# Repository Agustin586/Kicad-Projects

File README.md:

# Kicad-Projects
Aca se encuentran los diseños de pcb de kicad

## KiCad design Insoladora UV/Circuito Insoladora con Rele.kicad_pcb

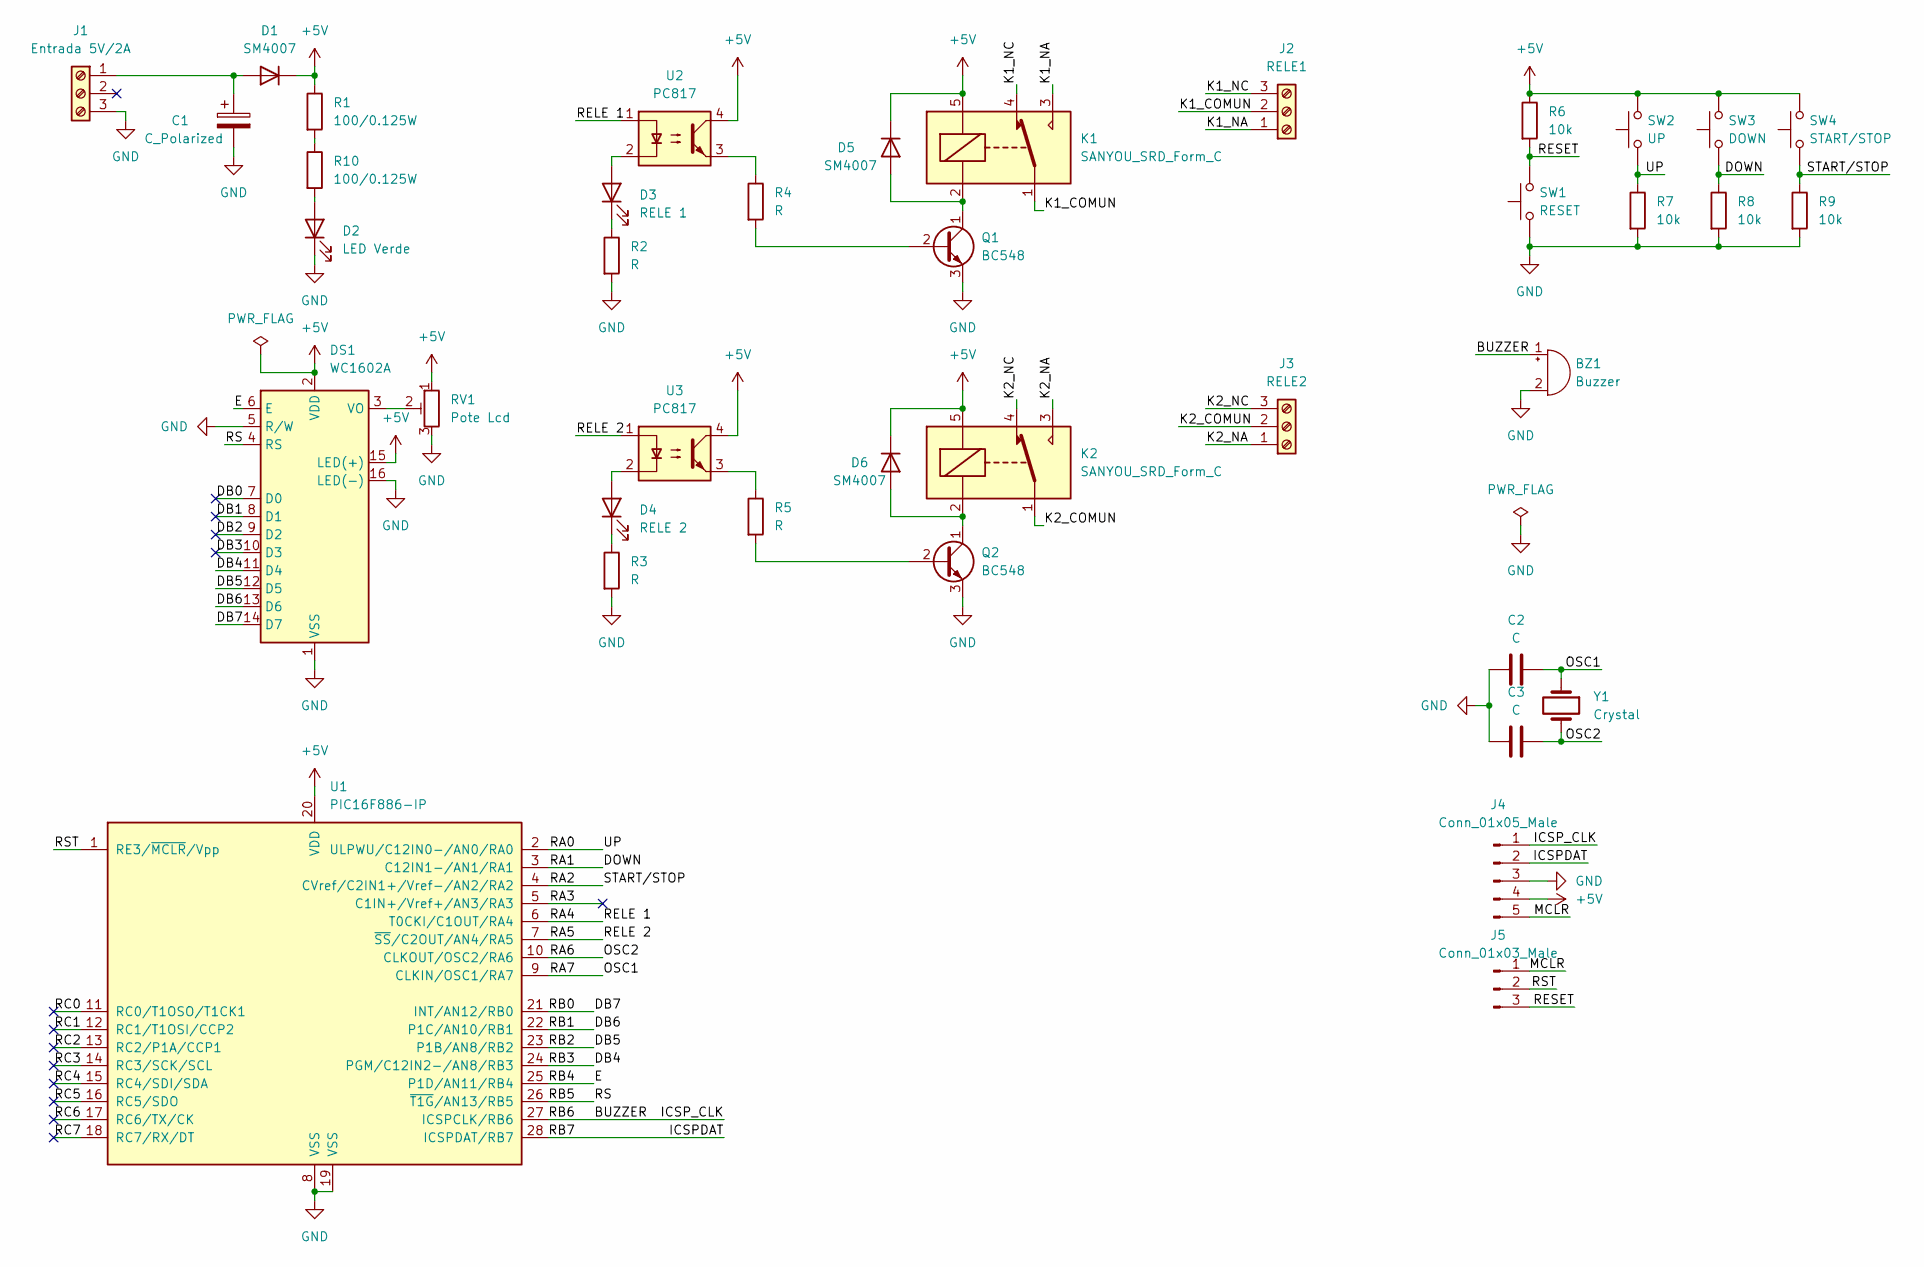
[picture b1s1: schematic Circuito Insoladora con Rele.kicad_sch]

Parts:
BZ1: Buzzer; Buzzer_12x9.5RM7.6
C1: C_Polarized; CP_Radial_D8.0mm_P2.50mm
C2, C3: C; C_Disc_D4.7mm_W2.5mm_P5.00mm
D1, D5, D6: SM4007; D_MELF
D2: LED Verde; LED_0805_2012Metric
D3: RELE 1; LED_D5.0mm
D4: RELE 2; LED_D5.0mm
DS1: WC1602A
J1: Entrada 5V/2A; TerminalBlock_Phoenix_PT-1,5-3-5.0-H_1x03_P5.00mm_Horizontal
J2: RELE1; TerminalBlock_Phoenix_PT-1,5-3-5.0-H_1x03_P5.00mm_Horizontal
J3: RELE2; TerminalBlock_Phoenix_PT-1,5-3-5.0-H_1x03_P5.00mm_Horizontal
J4: Conn_01x05_Male; PinHeader_1x05_P2.54mm_Vertical
J5: Conn_01x03_Male; PinHeader_1x03_P2.54mm_Vertical
K1, K2: SANYOU_SRD_Form_C; Relay_SPDT_SANYOU_SRD_Series_Form_C
Q1, Q2: BC548; TO-92_Inline_Wide
R1, R10: 100/0.125W; R_0805_2012Metric
R2, R3, R4, R5: R; R_Axial_DIN0207_L6.3mm_D2.5mm_P10.16mm_Horizontal
R6, R7, R8, R9: 10k; R_0805_2012Metric
RV1: Pote Lcd; Potentiometer_Piher_PT-10-H05_Horizontal
SW1: RESET; SW_PUSH_6mm
SW2: UP; SW_PUSH_6mm
SW3: DOWN; SW_PUSH_6mm
SW4: START/STOP; SW_PUSH_6mm
U1: PIC16F886-IP; DIP-28_W7.62mm_LongPads
U2, U3: PC817; DIP-4_W7.62mm_LongPads
Y1: Crystal; Crystal_HC52-8mm_Vertical

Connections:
+5V: D1.1 (K), D5.1 (K), D6.1 (K), DS1.2 (VDD), DS1.15 (LED(+)), J4.4, K1.5, K2.5, R1.1, R6.1, RV1.1, SW2.2, SW3.2, SW4.2, U1.20 (VDD), U2.4, U3.4
/DB0: DS1.7 (D0)
/DB1: DS1.8 (D1)
/DB2: DS1.9 (D2)
/DB3: DS1.10 (D3)
/DB4: DS1.11 (D4), U1.24 (PGM/C12IN2-/AN8/RB3)
/DB5: DS1.12 (D5), U1.23 (P1B/AN8/RB2)
/DB6: DS1.13 (D6), U1.22 (P1C/AN10/RB1)
/DB7: DS1.14 (D7), U1.21 (INT/AN12/RB0)
/DOWN: R8.1, SW3.1, U1.3 (C12IN1-/AN1/RA1)
/E: DS1.6 (E), U1.25 (P1D/AN11/RB4)
/ICSP_CLK: BZ1.1 (-), J4.1, U1.27 (ICSPCLK/RB6)
/K1_COMUN: J2.2, K1.1
/K1_NA: J2.1, K1.3
/K1_NC: J2.3, K1.4
/K2_COMUN: J3.2, K2.1
/K2_NA: J3.1, K2.3
/K2_NC: J3.3, K2.4
/MCLR: J4.5, J5.1
/OSC1: C2.2, U1.9 (CLKIN/OSC1/RA7), Y1.1
/OSC2: C3.2, U1.10 (CLKOUT/OSC2/RA6), Y1.2
/RA0: R7.1, SW2.1, U1.2 (ULPWU/C12IN0-/AN0/RA0)
/RA2: R9.1, SW4.1, U1.4 (CVref/C2IN1+/Vref-/AN2/RA2)
/RA3: U1.5 (C1IN+/Vref+/AN3/RA3)
/RA4: U1.6 (T0CKI/C1OUT/RA4), U2.1
/RA5: U1.7 (~SS/C2OUT/AN4/RA5), U3.1
/RB5: DS1.4 (RS), U1.26 (~T1G/AN13/RB5)
/RB7: J4.2, U1.28 (ICSPDAT/RB7)
/RC0: U1.11 (RC0/T1OSO/T1CK1)
/RC1: U1.12 (RC1/T1OSI/CCP2)
/RC2: U1.13 (RC2/P1A/CCP1)
/RC3: U1.14 (RC3/SCK/SCL)
/RC4: U1.15 (RC4/SDI/SDA)
/RC5: U1.16 (RC5/SDO)
/RC6: U1.17 (RC6/TX/CK)
/RC7: U1.18 (RC7/RX/DT)
/RESET: J5.3, R6.2, SW1.2
/RST: J5.2, U1.1 (RE3/~MCLR/Vpp)
GND: BZ1.2 (+), C1.2, C2.1, C3.1, D2.1 (K), DS1.1 (VSS), DS1.5 (R/W), DS1.16 (LED(-)), J1.3, J4.3, Q1.3 (E), Q2.3 (E), R2.2, R3.2, R7.2, R8.2, R9.2, RV1.3, SW1.1, U1.8 (VSS), U1.19 (VSS)
unnamed: C1.1, D1.2 (A), J1.1
unnamed: D2.2 (A), R10.2
unnamed: D3.1 (K), R2.1
unnamed: D3.2 (A), U2.2
unnamed: D4.1 (K), R3.1
unnamed: D4.2 (A), U3.2
unnamed: D5.2 (A), K1.2, Q1.1 (C)
unnamed: D6.2 (A), K2.2, Q2.1 (C)
unnamed: DS1.3 (VO), RV1.2
unnamed: Q1.2 (B), R4.2
unnamed: Q2.2 (B), R5.2
unnamed: R1.2, R10.1
unnamed: R4.1, U2.3
unnamed: R5.1, U3.3

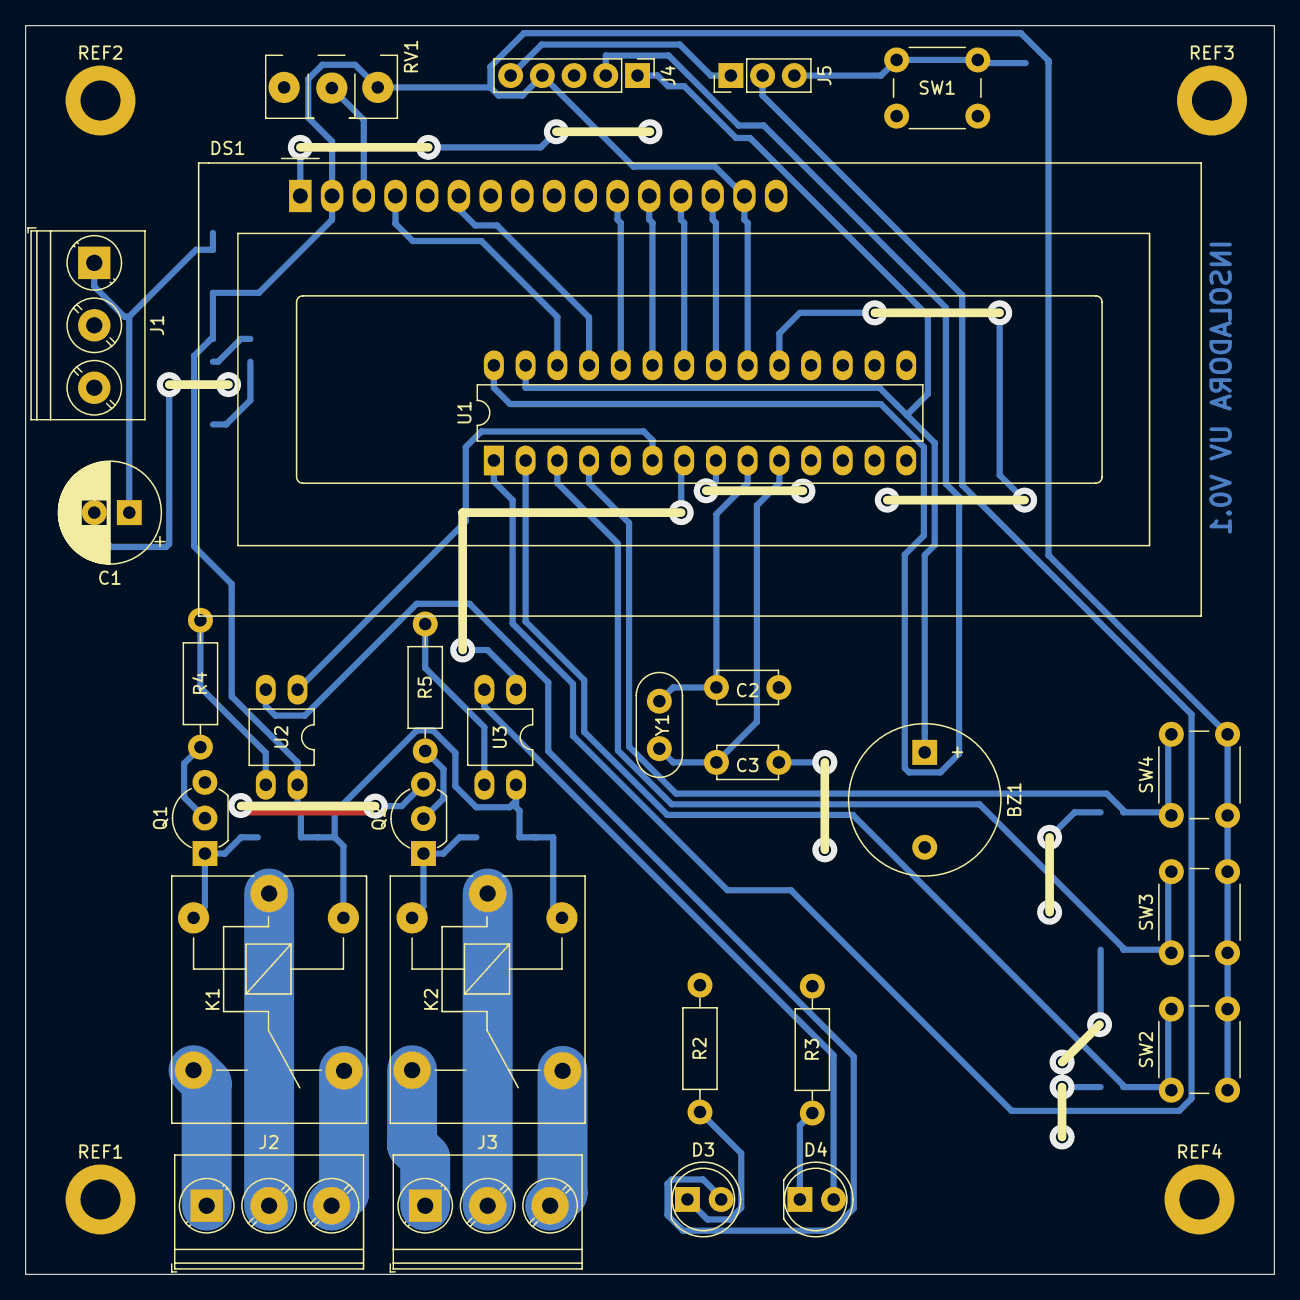
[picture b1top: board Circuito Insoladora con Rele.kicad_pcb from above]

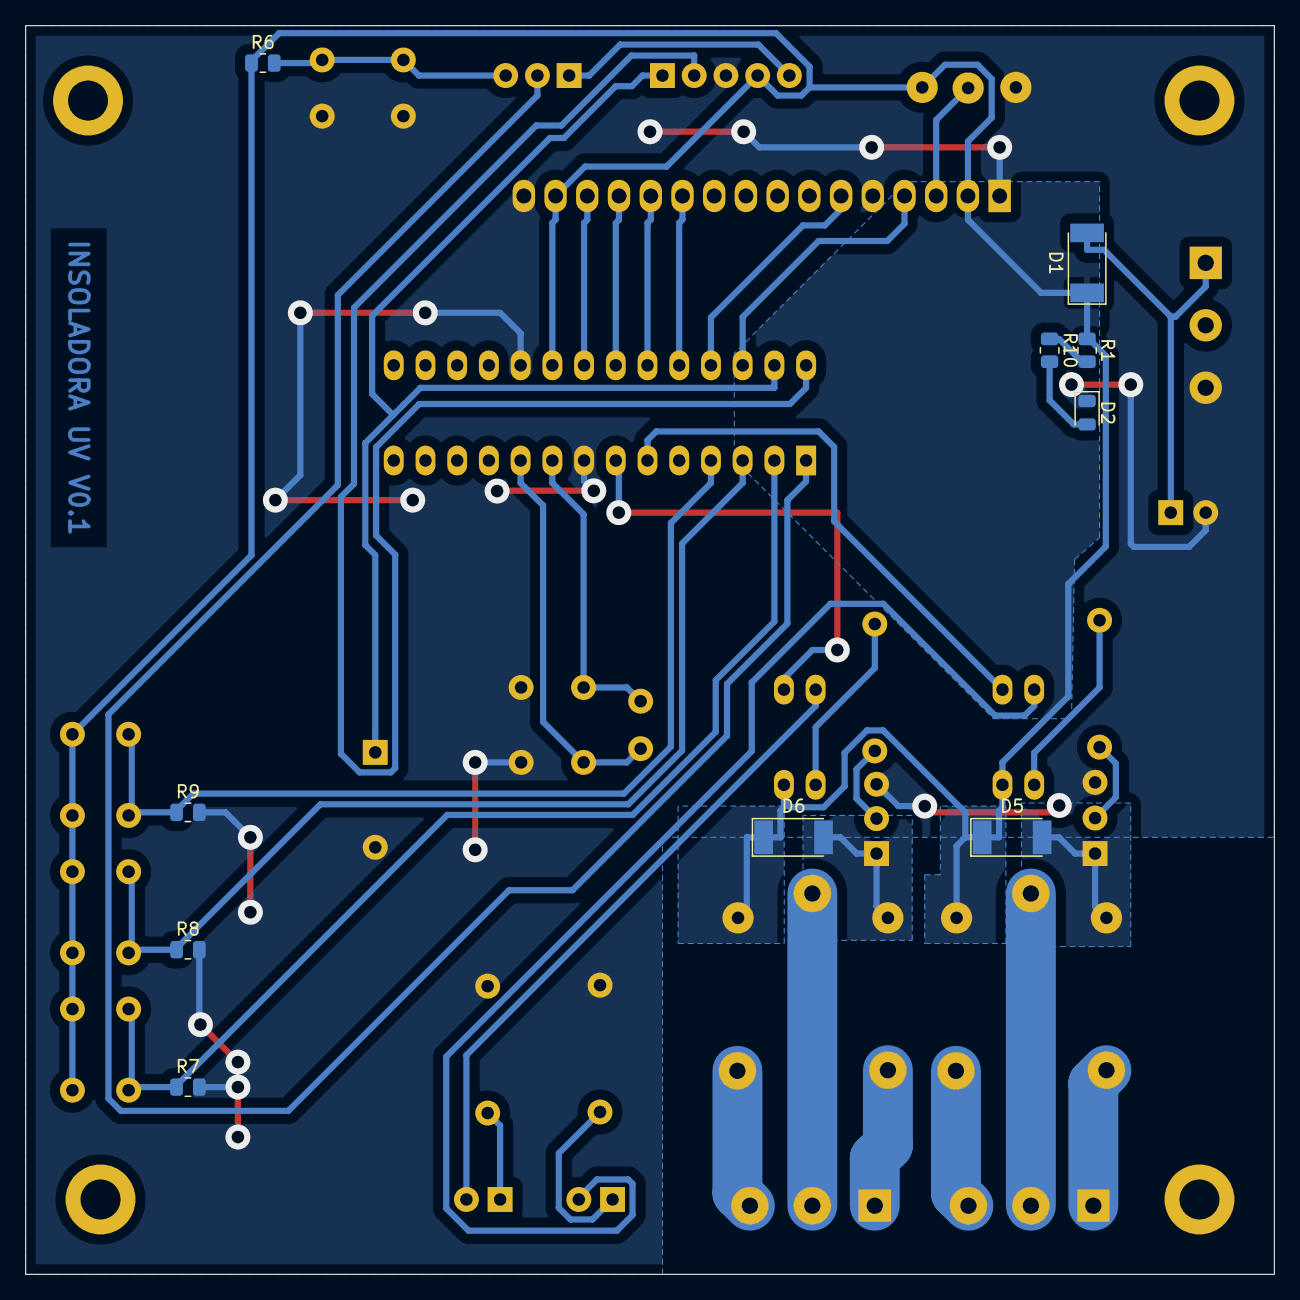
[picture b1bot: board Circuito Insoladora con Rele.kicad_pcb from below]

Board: 2 copper layers, 100.0 x 100.0 mm, 43 parts (10 on the bottom side), 40 nets.

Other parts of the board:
REF1, REF2, REF3, REF4: MountingHole_3.2mm_M3_DIN965_Pad

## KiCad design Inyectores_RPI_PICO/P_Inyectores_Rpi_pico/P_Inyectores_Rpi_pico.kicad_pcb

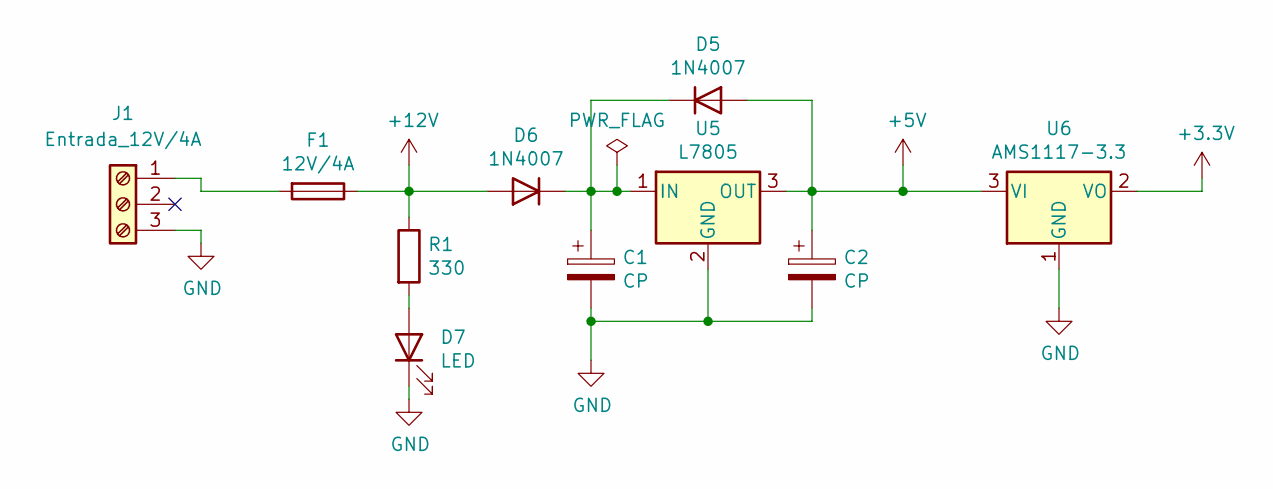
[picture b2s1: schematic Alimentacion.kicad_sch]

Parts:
C1, C2: CP; CP_Radial_D5.0mm_P2.00mm
D5, D6: 1N4007; D_DO-41_SOD81_P10.16mm_Horizontal
D7: LED; LED_D5.0mm
F1: 12V/4A; Fuse_SunFuse-6HP
J1: Entrada_12V/4A; TerminalBlock_Phoenix_PT-1,5-3-5.0-H_1x03_P5.00mm_Horizontal
R1: 330; R_Axial_DIN0207_L6.3mm_D2.5mm_P10.16mm_Horizontal
U5: L7805; TO-220-3_Vertical
U6: AMS1117-3.3; SOT-223-3_TabPin2

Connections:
+3V3: U6.2 (VO); also elsewhere on the board
+5V: C2.1, D5.2 (A), U5.3 (OUT), U6.3 (VI); also elsewhere on the board
+12V: D6.2 (A), F1.1, R1.1; also elsewhere on the board
GND: C1.2, C2.2, D7.1 (K), J1.3, U5.2 (GND), U6.1 (GND); also elsewhere on the board
unnamed: C1.1, D5.1 (K), D6.1 (K), U5.1 (IN)
unnamed: D7.2 (A), R1.2
unnamed: F1.2, J1.1

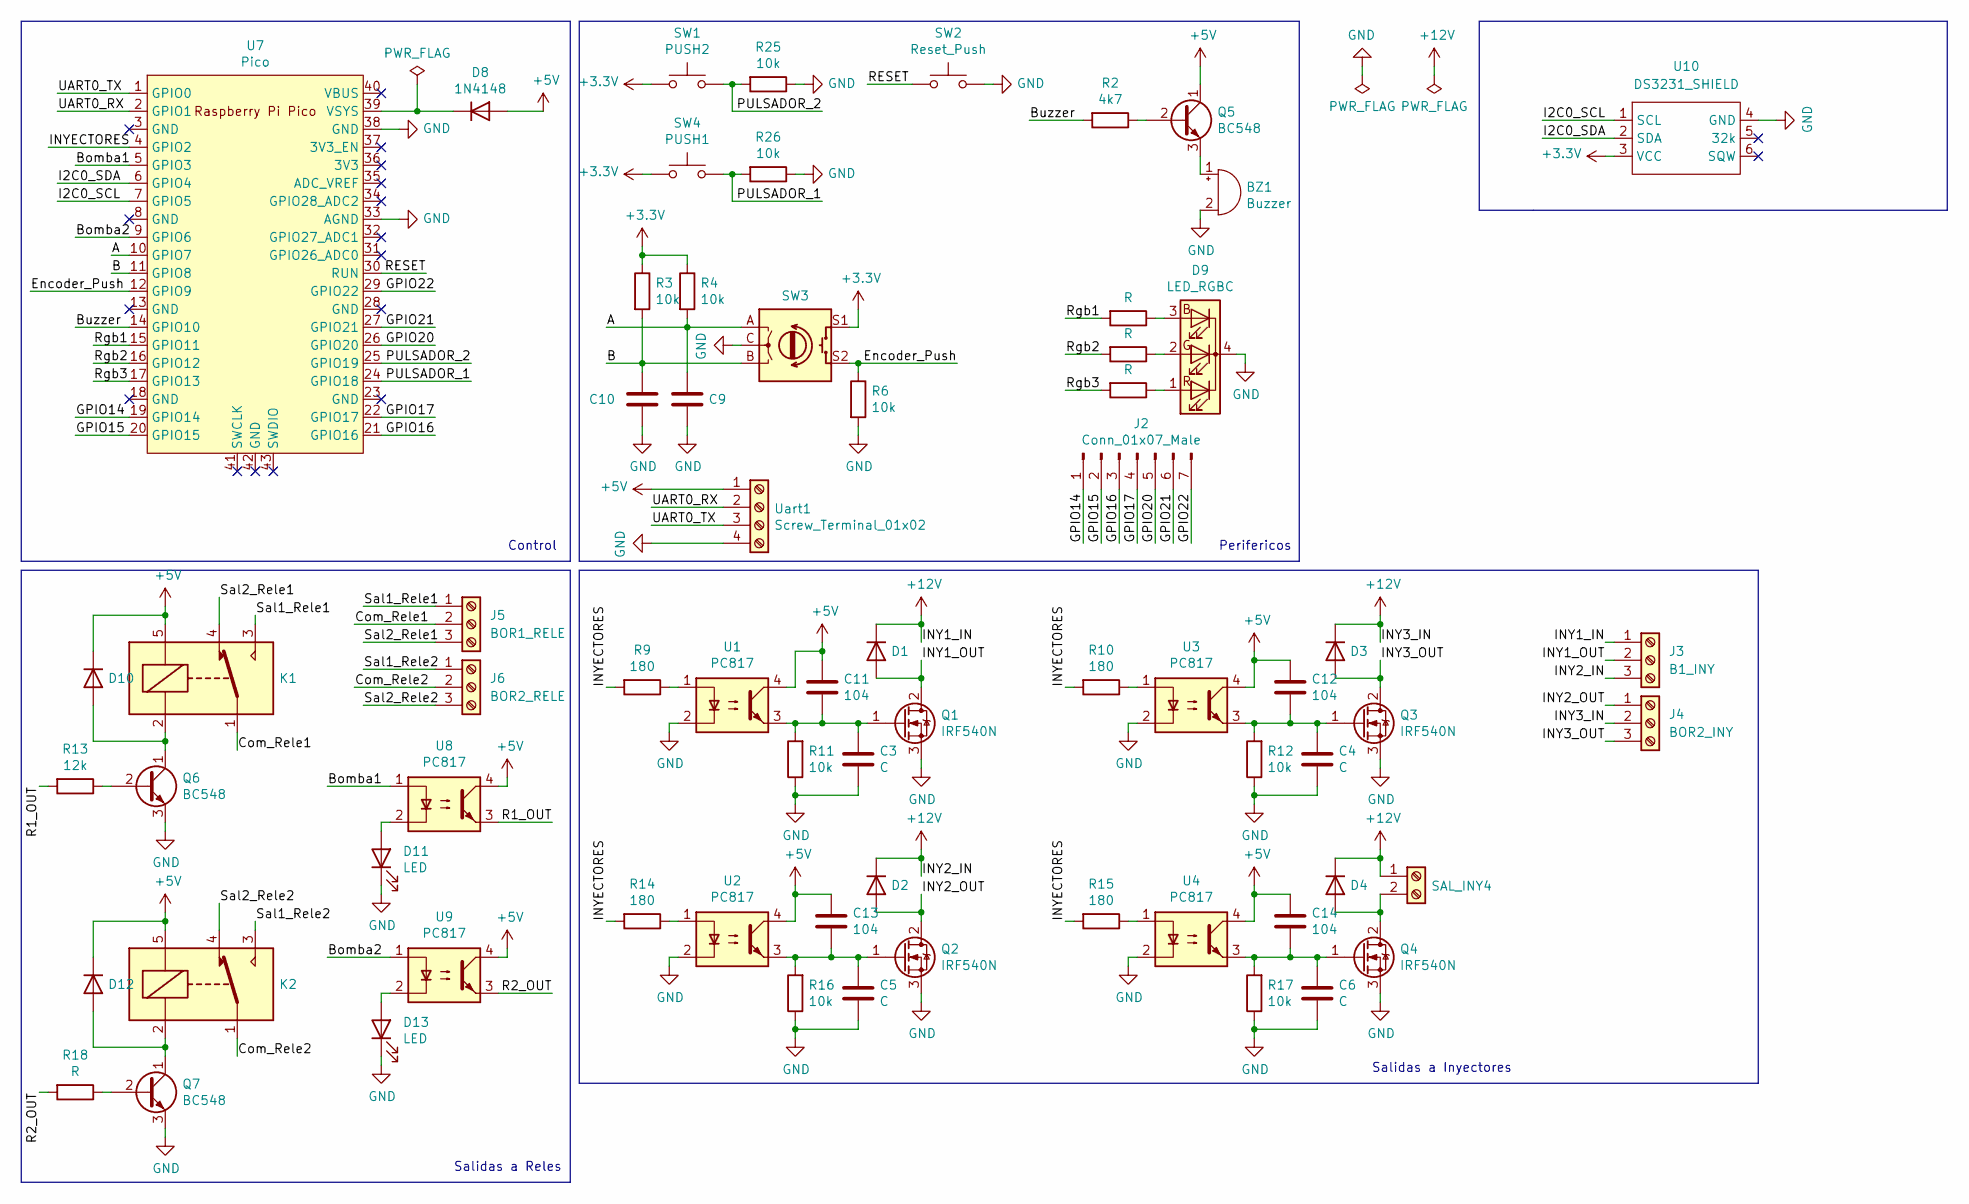
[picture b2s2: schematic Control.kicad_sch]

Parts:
BZ1: Buzzer; Buzzer_12x9.5RM7.6
C3, C4, C5, C6: C; C_Disc_D5.0mm_W2.5mm_P2.50mm
C9, C10, C11, C12, C13, C14: 104; C_Disc_D5.0mm_W2.5mm_P2.50mm
D1, D2, D3, D4, D10, D12: 1N4007; D_DO-41_SOD81_P10.16mm_Horizontal
D8: 1N4148; D_DO-35_SOD27_P7.62mm_Horizontal
D9: LED_RGBC; LED_D5.0mm-4_RGB_Wide_Pins
D11, D13: LED; LED_D5.0mm
J2: Conn_01x07_Male; PinSocket_1x07_P2.54mm_Vertical
J3: B1_INY; TerminalBlock_Phoenix_PT-1,5-3-5.0-H_1x03_P5.00mm_Horizontal
J4: BOR2_INY; TerminalBlock_Phoenix_PT-1,5-3-5.0-H_1x03_P5.00mm_Horizontal
J5: BOR1_RELE; TerminalBlock_Phoenix_PT-1,5-3-5.0-H_1x03_P5.00mm_Horizontal
J6: BOR2_RELE; TerminalBlock_Phoenix_PT-1,5-3-5.0-H_1x03_P5.00mm_Horizontal
K1, K2: SANYOU_SRD_Form_C; Relay_SPDT_SANYOU_SRD_Series_Form_C
Q1, Q2, Q3, Q4: IRF540N; TO-220-3_Vertical
Q5, Q6, Q7: BC548; TO-92_Inline_Wide
R2: 4k7; R_Axial_DIN0207_L6.3mm_D2.5mm_P10.16mm_Horizontal
R3, R4, R6, R11, R12, R16, R17, R25, R26: 10k; R_Axial_DIN0207_L6.3mm_D2.5mm_P10.16mm_Horizontal
R5, R7, R8, R18: R; R_Axial_DIN0207_L6.3mm_D2.5mm_P10.16mm_Horizontal
R9, R10, R14, R15: 180; R_Axial_DIN0207_L6.3mm_D2.5mm_P10.16mm_Horizontal
R13: 12k; R_Axial_DIN0207_L6.3mm_D2.5mm_P10.16mm_Horizontal
SAL_INY4: BOR3_INY; TerminalBlock_Phoenix_PT-1,5-2-5.0-H_1x02_P5.00mm_Horizontal
SW1: PUSH2; SW_PUSH_6mm
SW2: Reset_Push; SW_PUSH_6mm
SW3: Rotary_Encoder_Switch; RotaryEncoder_Alps_EC12E-Switch_Vertical_H20mm
SW4: PUSH1; SW_PUSH_6mm
U1, U2, U3, U4, U8, U9: PC817; DIP-4_W7.62mm_LongPads
U7: Pico; RPi_Pico_SMD_TH
U10: DS3231_SHIELD; DS3231_Shield
Uart1: Screw_Terminal_01x02; Molex_KK-254_AE-6410-04A_1x04_P2.54mm_Vertical

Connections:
+3V3: R3.1, R4.1, SW1.1, SW3.S1, SW4.1, U10.3 (VCC); also elsewhere on the board
+5V: C11.1, C12.1, C13.1, C14.1, D8.2 (A), D10.1 (K), D12.1 (K), K1.5, K2.5, Q5.1 (C), U1.4, U2.4, U3.4, U4.4, U8.4, U9.4, Uart1.1; also elsewhere on the board
+12V: D1.1 (K), D2.1 (K), D3.1 (K), D4.1 (K), J3.1, J3.3, J4.2, SAL_INY4.1; also elsewhere on the board
/Control/A: C9.1, R4.2, SW3.A, U7.10 (GPIO7)
/Control/B: C10.1, R3.2, SW3.B, U7.11 (GPIO8)
/Control/Bomba1: U7.5 (GPIO3), U8.1
/Control/Bomba2: U7.9 (GPIO6), U9.1
/Control/Buzzer: R2.2, U7.14 (GPIO10)
/Control/Com_Rele1: J5.2, K1.1
/Control/Com_Rele2: J6.2, K2.1
/Control/Encoder_Push: R6.1, SW3.S2, U7.12 (GPIO9)
/Control/GPIO14: J2.1, U7.19 (GPIO14)
/Control/GPIO15: J2.2, U7.20 (GPIO15)
/Control/GPIO16: J2.3, U7.21 (GPIO16)
/Control/GPIO17: J2.4, U7.22 (GPIO17)
/Control/GPIO20: J2.5, U7.26 (GPIO20)
/Control/GPIO21: J2.6, U7.27 (GPIO21)
/Control/GPIO22: J2.7, U7.29 (GPIO22)
/Control/I2C0_SCL: U7.7 (GPIO5), U10.1 (SCL)
/Control/I2C0_SDA: U7.6 (GPIO4), U10.2 (SDA)
/Control/INY1_OUT: D1.2 (A), J3.2, Q1.2 (D)
/Control/INY2_OUT: D2.2 (A), J4.1, Q2.2 (D)
/Control/INY3_OUT: D3.2 (A), J4.3, Q3.2 (D)
/Control/INYECTORES: R9.2, R10.2, R14.2, R15.2, U7.4 (GPIO2)
/Control/PULSADOR_1: R26.2, SW4.2, U7.24 (GPIO18)
/Control/PULSADOR_2: R25.2, SW1.2, U7.25 (GPIO19)
/Control/R1_OUT: R13.2, U8.3
/Control/R2_OUT: R18.2, U9.3
/Control/RESET: SW2.1, U7.30 (RUN)
/Control/Rgb1: R5.2, U7.15 (GPIO11)
/Control/Rgb2: R7.2, U7.16 (GPIO12)
/Control/Rgb3: R8.2, U7.17 (GPIO13)
/Control/Sal1_Rele1: J5.1, K1.3
/Control/Sal1_Rele2: J6.1, K2.3
/Control/Sal2_Rele1: J5.3, K1.4
/Control/Sal2_Rele2: J6.3, K2.4
/Control/UART0_RX: U7.2 (GPIO1), Uart1.2
/Control/UART0_TX: U7.1 (GPIO0), Uart1.3
GND: BZ1.2 (+), C3.2, C4.2, C5.2, C6.2, C9.2, C10.2, D9.4 (K), D11.1 (K), D13.1 (K), Q1.3 (S), Q2.3 (S), Q3.3 (S), Q4.3 (S), Q6.3 (E), Q7.3 (E), R6.2, R11.1, R12.1, R16.1, R17.1, R25.1, R26.1, SW2.2, SW3.C, U1.2, U2.2, U3.2, U4.2, U7.33 (AGND), U7.38 (GND), U10.4 (GND), Uart1.4; also elsewhere on the board
unnamed: BZ1.1 (-), Q5.3 (E)
unnamed: C3.1, C11.2, Q1.1 (G), R11.2, U1.3
unnamed: C4.1, C12.2, Q3.1 (G), R12.2, U3.3
unnamed: C5.1, C13.2, Q2.1 (G), R16.2, U2.3
unnamed: C6.1, C14.2, Q4.1 (G), R17.2, U4.3
unnamed: D4.2 (A), Q4.2 (D), SAL_INY4.2
unnamed: D8.1 (K), U7.39 (VSYS)
unnamed: D9.1 (RA), R8.1
unnamed: D9.2 (GA), R7.1
unnamed: D9.3 (BA), R5.1
unnamed: D10.2 (A), K1.2, Q6.1 (C)
unnamed: D11.2 (A), U8.2
unnamed: D12.2 (A), K2.2, Q7.1 (C)
unnamed: D13.2 (A), U9.2
unnamed: Q5.2 (B), R2.1
unnamed: Q6.2 (B), R13.1
unnamed: Q7.2 (B), R18.1
unnamed: R9.1, U1.1
unnamed: R10.1, U3.1
unnamed: R14.1, U2.1
unnamed: R15.1, U4.1

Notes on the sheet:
Salidas a Inyectores
Control
Salidas a Reles
Perifericos

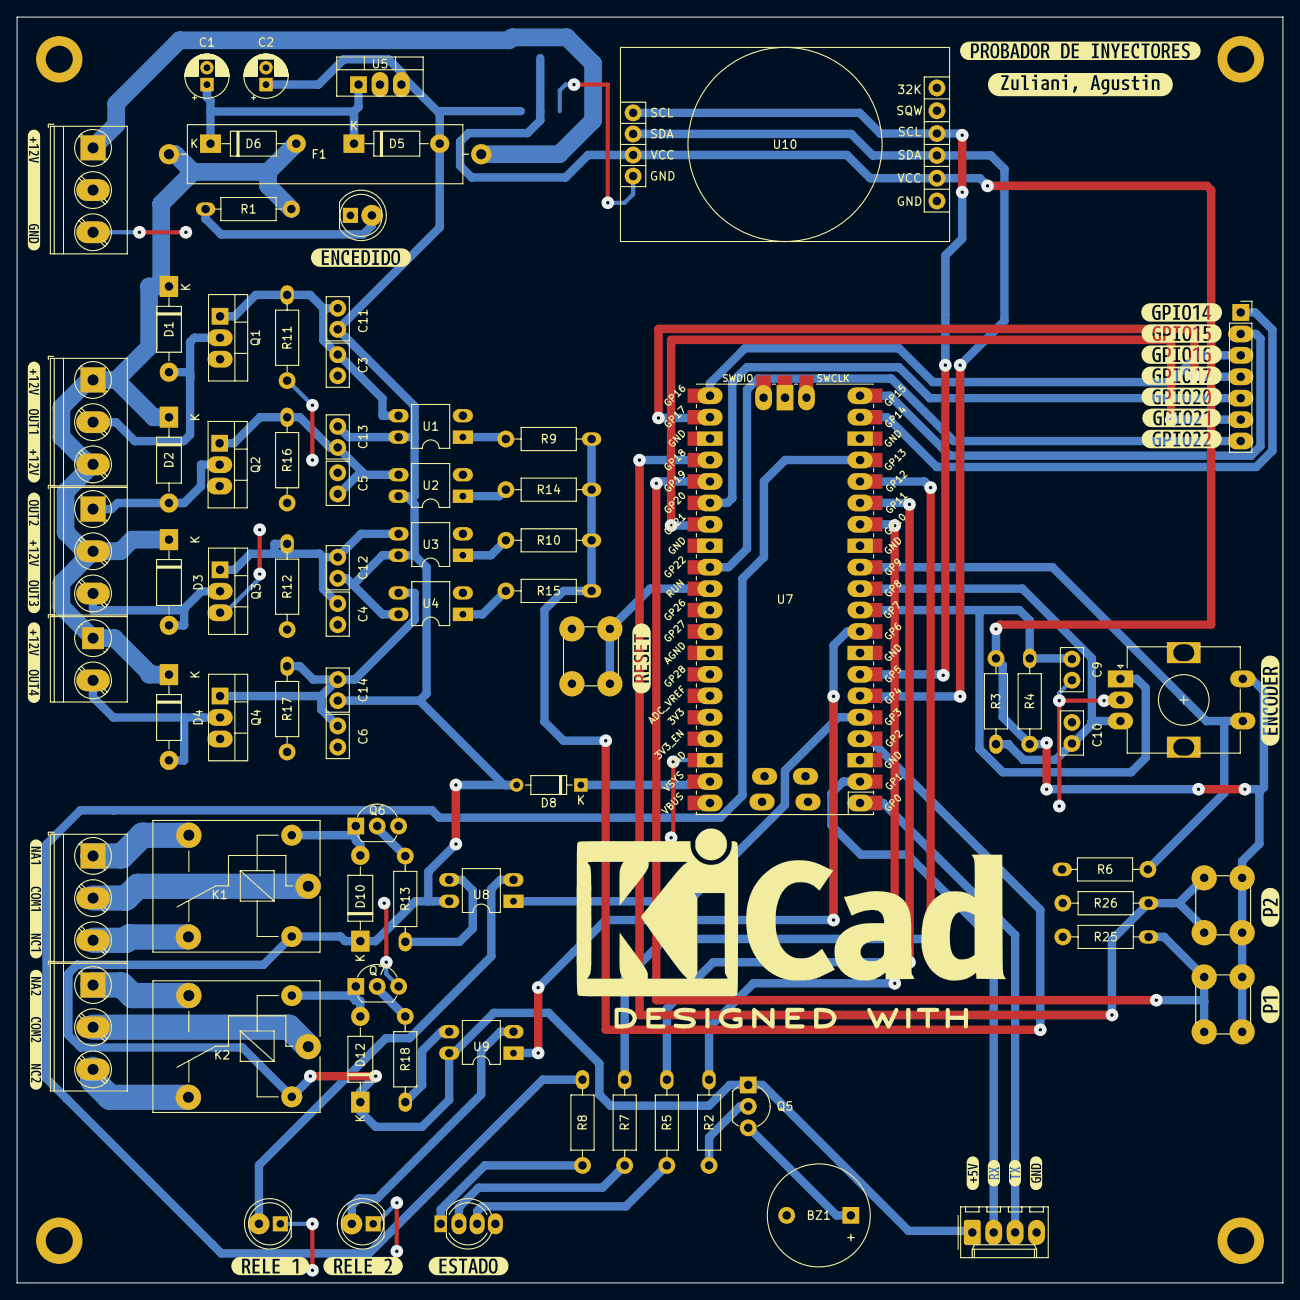
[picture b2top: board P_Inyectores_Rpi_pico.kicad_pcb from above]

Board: 2 copper layers, 150.0 x 150.0 mm, 109 parts (1 on the bottom side), 63 nets.

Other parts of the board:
REF1: KiCad-Logo2_20mm_SilkScree; KiCad-Logo2_20mm_SilkScreen
REF3, REF4, REF5: MountingHole_3.2mm_M3_ISO14580_Pad
kibuzzard-62C09A4A: G***; kibuzzard-62C09A4A
kibuzzard-62C09A65: G***; kibuzzard-62C09A65
kibuzzard-62C095A2: G***; kibuzzard-62C095A2
kibuzzard-62C095AC: G***; kibuzzard-62C095AC
kibuzzard-62C095B6: G***; kibuzzard-62C095B6
kibuzzard-62C095BF: G***; kibuzzard-62C095BF
kibuzzard-62C095C6: G***; kibuzzard-62C095C6
kibuzzard-62C095D0: G***; kibuzzard-62C095D0
kibuzzard-62C095D9: G***; kibuzzard-62C095D9
kibuzzard-62C096C0: G***; kibuzzard-62C096C0
kibuzzard-62C096D5: G***; kibuzzard-62C096D5
kibuzzard-62C096DE: G***; kibuzzard-62C096DE
kibuzzard-62C096F9: G***; kibuzzard-62C096F9
kibuzzard-62C098BB: G***; kibuzzard-62C098BB
kibuzzard-62C099B8: G***; kibuzzard-62C099B8
kibuzzard-62C099BF: G***; kibuzzard-62C099BF
kibuzzard-62C099C8: G***; kibuzzard-62C099C8
kibuzzard-62C099DD: G***; kibuzzard-62C099DD
kibuzzard-62C0966F: G***; kibuzzard-62C0966F
kibuzzard-62C09447: G***; kibuzzard-62C09447
kibuzzard-62C09473: G***; kibuzzard-62C09473
kibuzzard-62C09649: G***; kibuzzard-62C09649
kibuzzard-62C09656: G***; kibuzzard-62C09656
kibuzzard-62C09664: G***; kibuzzard-62C09664
kibuzzard-62C09818: G***; kibuzzard-62C09818
kibuzzard-62C09846: G***; kibuzzard-62C09846
kibuzzard-62C09983: G***; kibuzzard-62C09983

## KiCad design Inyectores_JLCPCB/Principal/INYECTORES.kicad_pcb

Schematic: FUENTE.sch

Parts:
D7, D9: 1N5408; D_DO-201AD_P15.24mm_Horizontal
D8: 1N4007; D_DO-41_SOD81_P10.16mm_Horizontal
ENTRADA_RELE1: Screw_Terminal_01x02; bornera_tornillos_1x02
J1: Screw_Terminal_01x03; bornera_tornillos_1x03
R1, R2: 440; R_Axial_DIN0207_L6.3mm_D2.5mm_P10.16mm_Horizontal
RL1: JW2; Relay_DPDT_Panasonic_JW2
ROJO1: LED; LED_D5.0mm
SALIDA_RELE1: Screw_Terminal_01x02; bornera_tornillos_1x02
SW1: SW_Push; SW_PUSH_6mm
VERDE1: LED; LED_D5.0mm

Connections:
unnamed 30: D7.2 (A), ENTRADA_RELE1.1; also elsewhere on the board
unnamed 46: R1.1; also elsewhere on the board
RELE1: R2.2, VERDE1.2 (A); also elsewhere on the board
RELE2: R1.2, ROJO1.2 (A); also elsewhere on the board

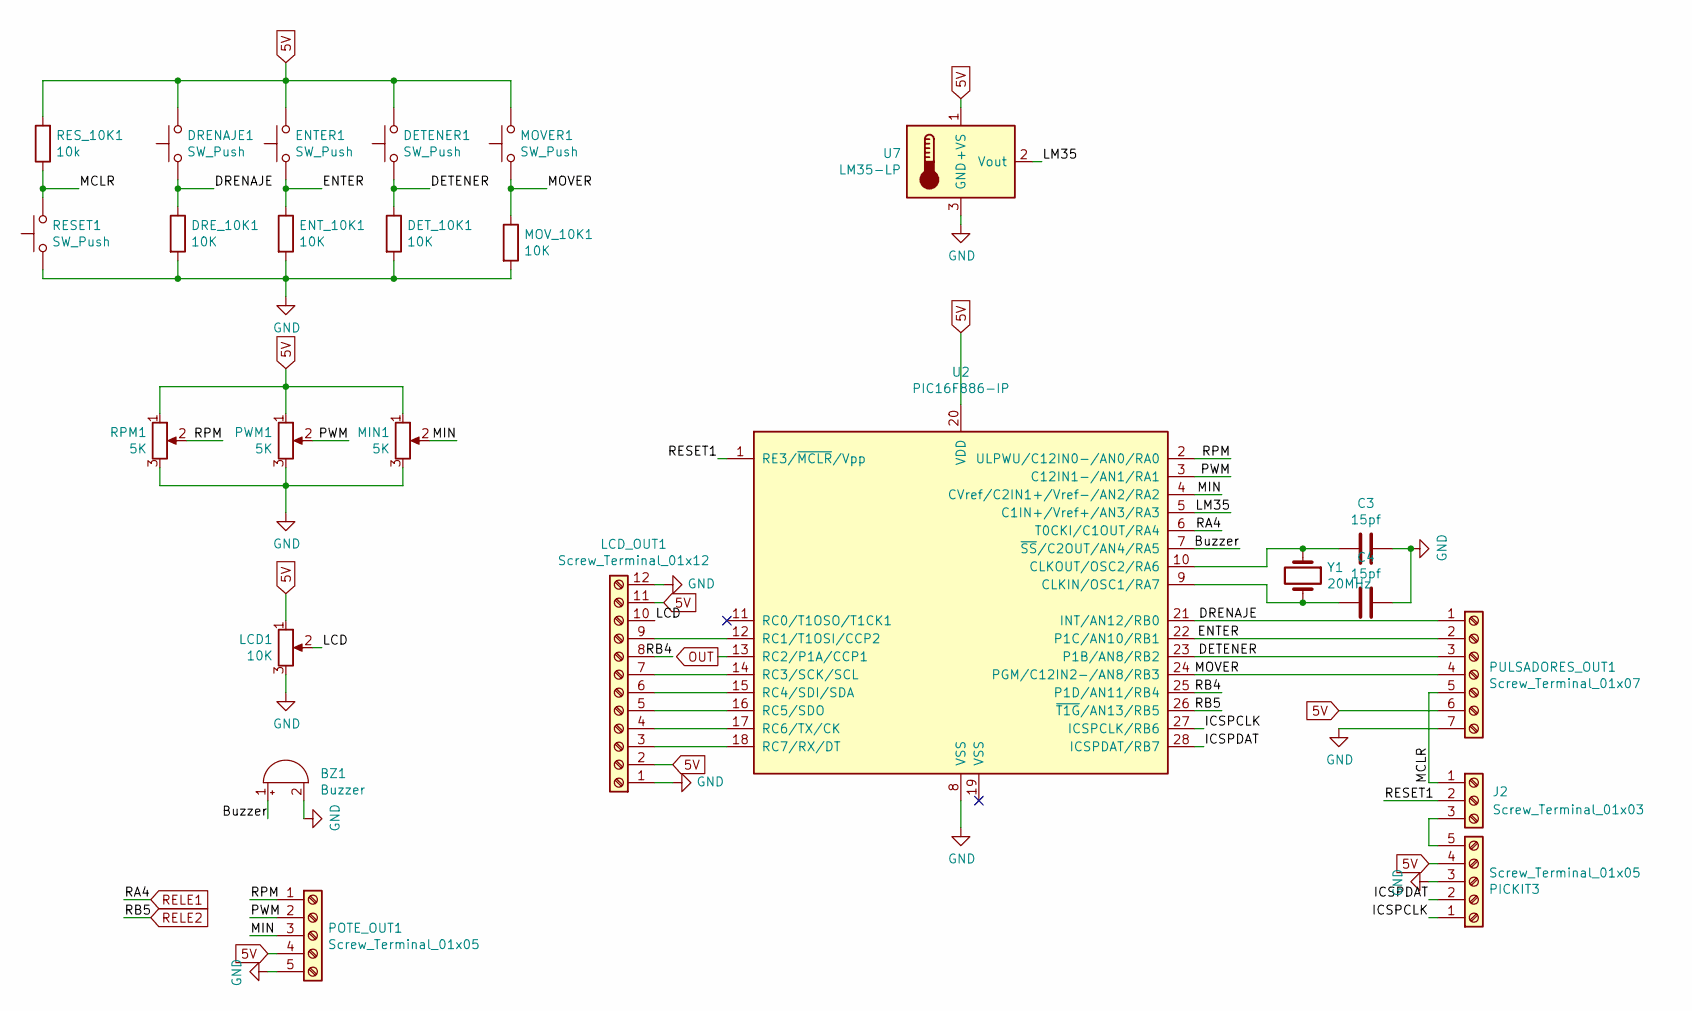
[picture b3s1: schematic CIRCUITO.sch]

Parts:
BZ1: Buzzer; Buzzer_12x9.5RM7.6
C3, C4: 15pf; C_Disc_D3.0mm_W2.0mm_P2.50mm
DETENER1: SW_Push; SW_PUSH_6mm
DET_10K1: 10K; R_Axial_DIN0207_L6.3mm_D2.5mm_P10.16mm_Horizontal
DRENAJE1: SW_Push; SW_PUSH_6mm
DRE_10K1: 10K; R_Axial_DIN0207_L6.3mm_D2.5mm_P10.16mm_Horizontal
ENTER1: SW_Push; SW_PUSH_6mm
ENT_10K1: 10K; R_Axial_DIN0207_L6.3mm_D2.5mm_P10.16mm_Horizontal
J2: Screw_Terminal_01x03; PinHeader_1x03_P2.54mm_Vertical
LCD1: 10K; Potentiometer_Bourns_3296W_Vertical
LCD_OUT1: Screw_Terminal_01x12; PinSocket_1x12_P2.54mm_Vertical
MIN1: 5K; Potentiometer_Alps_RK163_Single_Horizontal
MOVER1: SW_Push; SW_PUSH_6mm
MOV_10K1: 10K; R_Axial_DIN0207_L6.3mm_D2.5mm_P10.16mm_Horizontal
PICKIT3: Screw_Terminal_01x05; PinHeader_1x05_P2.54mm_Horizontal
POTE_OUT1: Screw_Terminal_01x05; PinSocket_1x05_P2.54mm_Vertical
PULSADORES_OUT1: Screw_Terminal_01x07; PinSocket_1x07_P2.54mm_Vertical
PWM1: 5K; Potentiometer_Alps_RK163_Single_Horizontal
RESET1: SW_Push; SW_PUSH_6mm
RES_10K1: 10k; R_Axial_DIN0207_L6.3mm_D2.5mm_P10.16mm_Horizontal
RPM1: 5K; Potentiometer_Alps_RK163_Single_Horizontal
U2: PIC16F886-IP; DIP-28_W7.62mm_LongPads
U7: LM35-LP; TO-92L_Inline_Wide
Y1: 20MHz; Crystal_HC18-U_Vertical

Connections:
5V: DETENER1.2, DRENAJE1.2, ENTER1.2, LCD1.1, LCD_OUT1.2, LCD_OUT1.11, MIN1.1, MOVER1.2, PICKIT3.4, POTE_OUT1.4, PULSADORES_OUT1.6, PWM1.1, RES_10K1.2, RPM1.1, U2.20 (VDD), U7.1 (+VS); also elsewhere on the board
/CIRCUITO/Buzzer: BZ1.1 (-), U2.7 (~SS~/C2OUT/AN4/RA5)
/CIRCUITO/DETENER: DETENER1.1, DET_10K1.1, PULSADORES_OUT1.3, U2.23 (P1B/AN8/RB2)
/CIRCUITO/DRENAJE: DRENAJE1.1, DRE_10K1.1, PULSADORES_OUT1.1, U2.21 (INT/AN12/RB0)
/CIRCUITO/ENTER: ENTER1.1, ENT_10K1.1, PULSADORES_OUT1.2, U2.22 (P1C/AN10/RB1)
/CIRCUITO/ICSPCLK: PICKIT3.1, U2.27 (ICSPCLK/RB6)
/CIRCUITO/ICSPDAT: PICKIT3.2, U2.28 (ICSPDAT/RB7)
/CIRCUITO/LCD: LCD1.2, LCD_OUT1.10
/CIRCUITO/LM35: U2.5 (C1IN+/Vref+/AN3/RA3), U7.2 (Vout)
/CIRCUITO/MCLR: J2.1, PULSADORES_OUT1.5, RESET1.2, RES_10K1.1
/CIRCUITO/MIN: MIN1.2, POTE_OUT1.3, U2.4 (CVref/C2IN1+/Vref-/AN2/RA2)
/CIRCUITO/MOVER: MOVER1.1, MOV_10K1.1, PULSADORES_OUT1.4, U2.24 (PGM/C12IN2-/AN8/RB3)
/CIRCUITO/PWM: POTE_OUT1.2, PWM1.2, U2.3 (C12IN1-/AN1/RA1)
/CIRCUITO/RB4: LCD_OUT1.8, U2.25 (P1D/AN11/RB4)
/CIRCUITO/RESET1: J2.2, U2.1 (RE3/~MCLR~/Vpp)
/CIRCUITO/RPM: POTE_OUT1.1, RPM1.2, U2.2 (ULPWU/C12IN0-/AN0/RA0)
unnamed: C3.2, U2.10 (CLKOUT/OSC2/RA6), Y1.1
unnamed: C4.2, U2.9 (CLKIN/OSC1/RA7), Y1.2
unnamed: J2.3, PICKIT3.5
unnamed: LCD_OUT1.3, U2.18 (RC7/RX/DT)
unnamed: LCD_OUT1.4, U2.17 (RC6/TX/CK)
unnamed: LCD_OUT1.5, U2.16 (RC5/SDO)
unnamed: LCD_OUT1.6, U2.15 (RC4/SDI/SDA)
unnamed: LCD_OUT1.7, U2.14 (RC3/SCK/SCL)
unnamed: LCD_OUT1.9, U2.12 (RC1/T1OSI/CCP2)
OUT: U2.13 (RC2/P1A/CCP1); also elsewhere on the board
RELE1: U2.6 (T0CKI/C1OUT/RA4); also elsewhere on the board
RELE2: U2.26 (~T1G~/AN13/RB5); also elsewhere on the board
